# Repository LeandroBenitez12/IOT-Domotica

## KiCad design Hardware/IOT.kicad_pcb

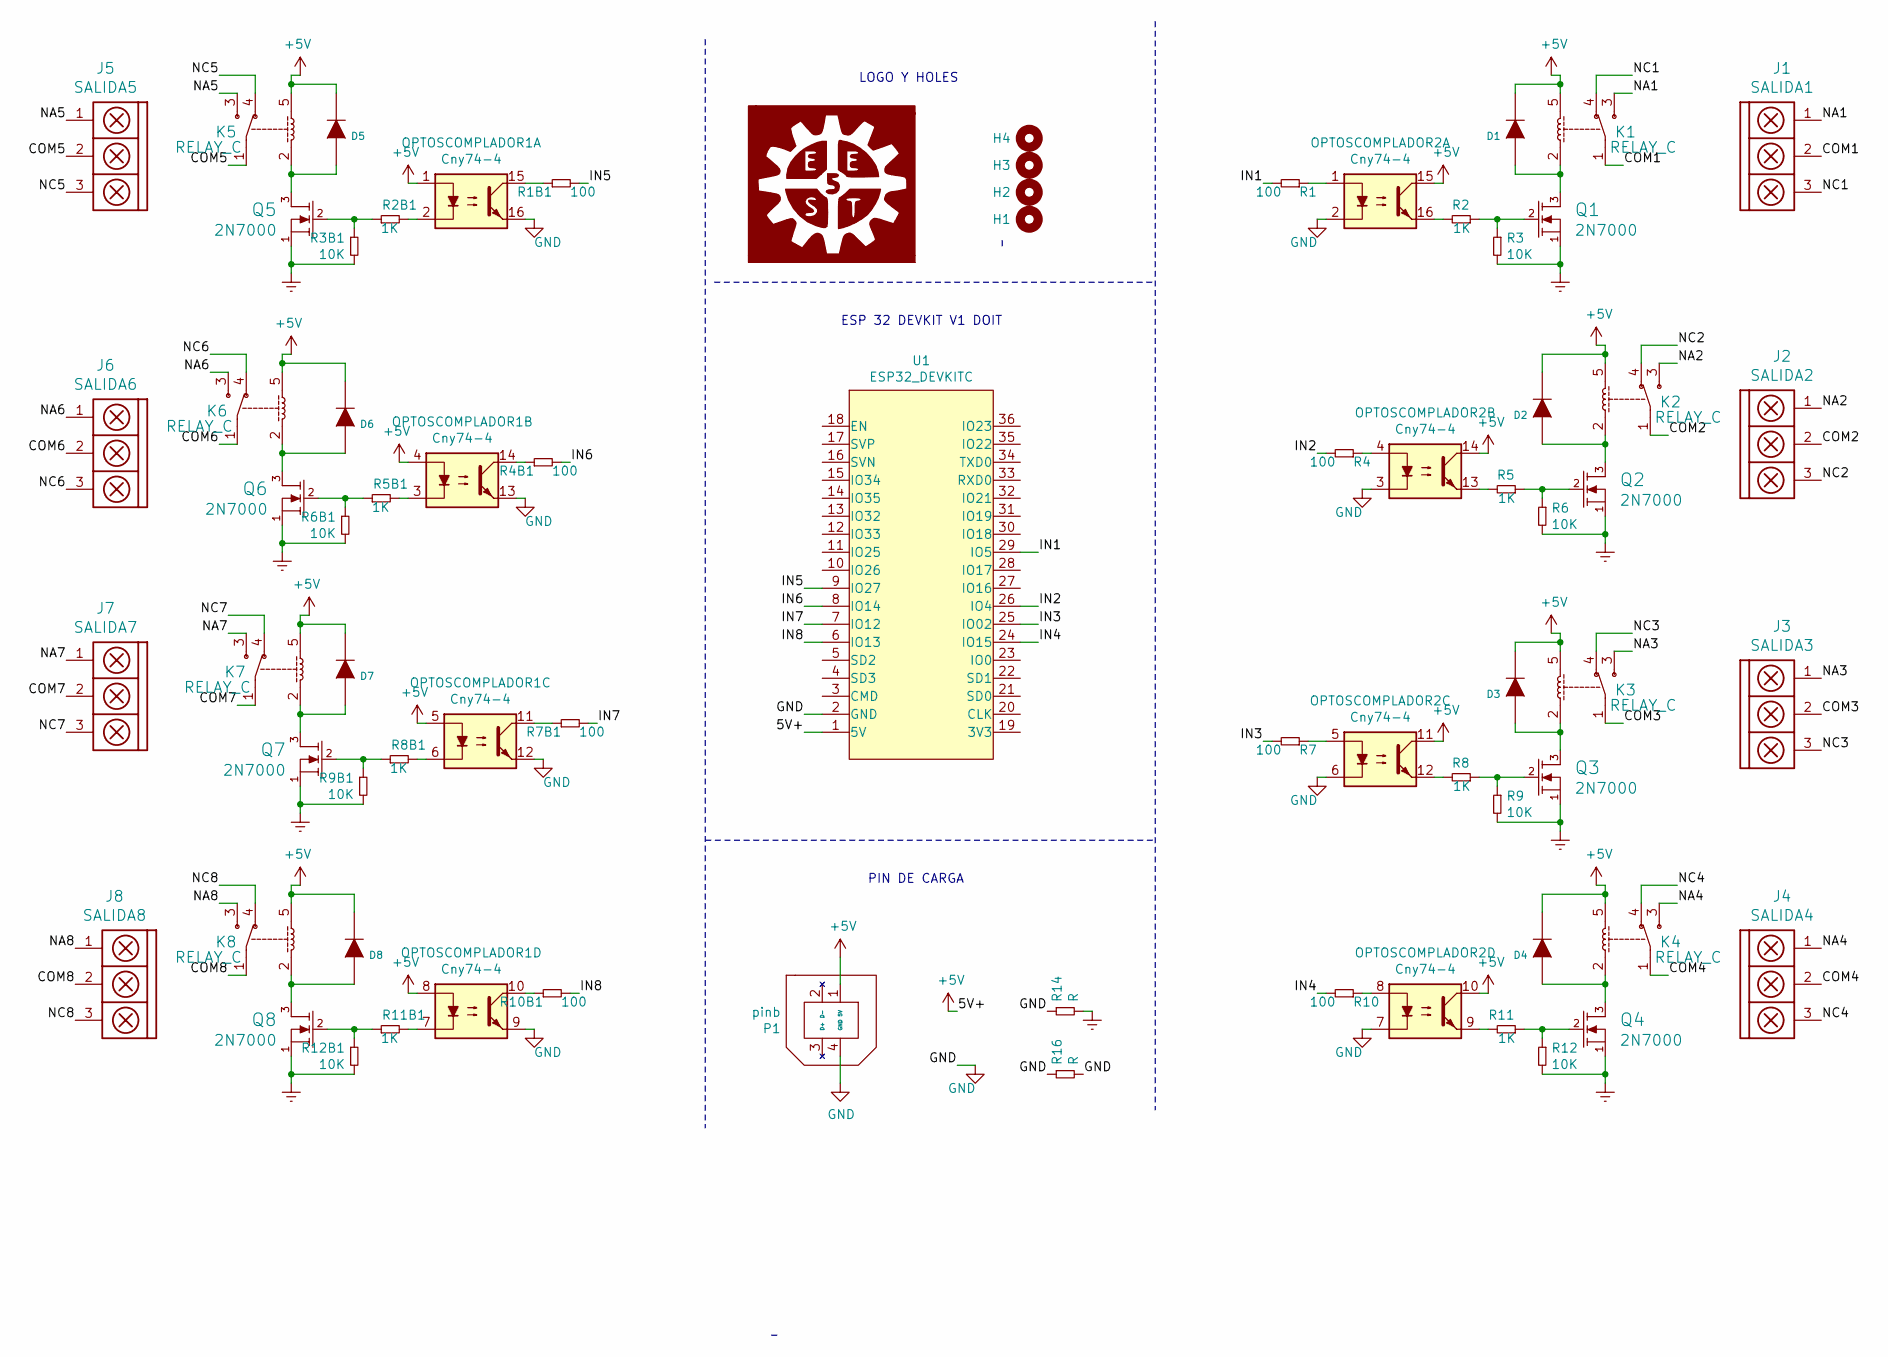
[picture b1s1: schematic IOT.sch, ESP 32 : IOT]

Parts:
D1, D2, D3, D4, D5, D6, D7, D8: DIODE; DO-41
G1: Logo_EESTN5; LOGO_EESTN5
H1, H2, H3, H4: Mounting_Hole; hole_2mm
J1: SALIDA1; BORNERA3_AZUL
J2: SALIDA2; BORNERA3_AZUL
J3: SALIDA3; BORNERA3_AZUL
J4: SALIDA4; BORNERA3_AZUL
J5: SALIDA5; BORNERA3_AZUL
J6: SALIDA6; BORNERA3_AZUL
J7: SALIDA7; BORNERA3_AZUL
J8: SALIDA8; BORNERA3_AZUL
K1, K2, K3, K4, K5, K6, K7, K8: RELAY_C; Relay_C
OPTOSCOMPLADOR1, OPTOSCOMPLADOR2: Cny74-4; DIP_16-300
P1: pinb; USB_B
Q1, Q2, Q3, Q4, Q5, Q6, Q7, Q8: 2N7000; to92
R1, R1B1, R4, R4B1, R7, R7B1, R10, R10B1: 100; RES0.3
R2, R2B1, R5, R5B1, R8, R8B1, R11, R11B1: 1K; RES0.3
R3, R3B1, R6, R6B1, R9, R9B1, R12, R12B1: 10K; RES0.3
R14, R16: R; RES0.3
U1: ESP32_DEVKITC; ESP32_DEVKITC1

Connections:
+5V: D1.2 (K), D2.2 (K), D3.2 (K), D4.2 (K), D5.2 (K), D6.2 (K), D7.2 (K), D8.2 (K), K1.5, K2.5, K3.5, K4.5, K5.5, K6.5, K7.5, K8.5, OPTOSCOMPLADOR1.1, OPTOSCOMPLADOR1.4, OPTOSCOMPLADOR1.5, OPTOSCOMPLADOR1.8, OPTOSCOMPLADOR2.10, OPTOSCOMPLADOR2.11, OPTOSCOMPLADOR2.14, OPTOSCOMPLADOR2.15, P1.1 (5V), U1.1 (5V)
/COM1: J1.2, K1.1
/COM2: J2.2, K2.1
/COM3: J3.2, K3.1
/COM4: J4.2, K4.1
/COM5: J5.2, K5.1
/COM6: J6.2, K6.1
/COM7: J7.2, K7.1
/COM8: J8.2, K8.1
/IN1: R1.2, U1.29 (IO5)
/IN2: R4.2, U1.26 (IO4)
/IN3: R7.2, U1.25 (IO02)
/IN4: R10.2, U1.24 (IO15)
/IN5: R1B1.2, U1.9 (IO27)
/IN6: R4B1.2, U1.8 (IO14)
/IN7: R7B1.2, U1.7 (IO12)
/IN8: R10B1.2, U1.6 (IO13)
/NA1: J1.1, K1.3
/NA2: J2.1, K2.3
/NA3: J3.1, K3.3
/NA4: J4.1, K4.3
/NA5: J5.1, K5.3
/NA6: J6.1, K6.3
/NA7: J7.1, K7.3
/NA8: J8.1, K8.3
/NC1: J1.3, K1.4
/NC2: J2.3, K2.4
/NC3: J3.3, K3.4
/NC4: J4.3, K4.4
/NC5: J5.3, K5.4
/NC6: J6.3, K6.4
/NC7: J7.3, K7.4
/NC8: J8.3, K8.4
GND: OPTOSCOMPLADOR1.9, OPTOSCOMPLADOR1.12, OPTOSCOMPLADOR1.13, OPTOSCOMPLADOR1.16, OPTOSCOMPLADOR2.2, OPTOSCOMPLADOR2.3, OPTOSCOMPLADOR2.6, OPTOSCOMPLADOR2.7, P1.4 (GND), R14.1, R16.1, R16.2, U1.2 (GND)
unnamed: D1.1 (A), K1.2, Q1.3 (D)
unnamed: D2.1 (A), K2.2, Q2.3 (D)
unnamed: D3.1 (A), K3.2, Q3.3 (D)
unnamed: D4.1 (A), K4.2, Q4.3 (D)
unnamed: D5.1 (A), K5.2, Q5.3 (D)
unnamed: D6.1 (A), K6.2, Q6.3 (D)
unnamed: D7.1 (A), K7.2, Q7.3 (D)
unnamed: D8.1 (A), K8.2, Q8.3 (D)
unnamed: OPTOSCOMPLADOR1.2, R2B1.2
unnamed: OPTOSCOMPLADOR1.3, R5B1.2
unnamed: OPTOSCOMPLADOR1.6, R8B1.2
unnamed: OPTOSCOMPLADOR1.7, R11B1.2
unnamed: OPTOSCOMPLADOR1.10, R10B1.1
unnamed: OPTOSCOMPLADOR1.11, R7B1.1
unnamed: OPTOSCOMPLADOR1.14, R4B1.1
unnamed: OPTOSCOMPLADOR1.15, R1B1.1
unnamed: OPTOSCOMPLADOR2.1, R1.1
unnamed: OPTOSCOMPLADOR2.4, R4.1
unnamed: OPTOSCOMPLADOR2.5, R7.1
unnamed: OPTOSCOMPLADOR2.8, R10.1
unnamed: OPTOSCOMPLADOR2.9, R11.2
unnamed: OPTOSCOMPLADOR2.12, R8.2
unnamed: OPTOSCOMPLADOR2.13, R5.2
unnamed: OPTOSCOMPLADOR2.16, R2.2
unnamed: Q1.2 (G), R2.1, R3.1
unnamed: Q2.2 (G), R5.1, R6.1
unnamed: Q3.2 (G), R8.1, R9.1
unnamed: Q4.2 (G), R11.1, R12.1
unnamed: Q5.2 (G), R2B1.1, R3B1.1
unnamed: Q6.2 (G), R5B1.1, R6B1.1
unnamed: Q7.2 (G), R8B1.1, R9B1.1
unnamed: Q8.2 (G), R11B1.1, R12B1.1

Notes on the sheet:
ESP 32 DEVKIT V1 DOIT
LOGO Y HOLES
PIN DE CARGA

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
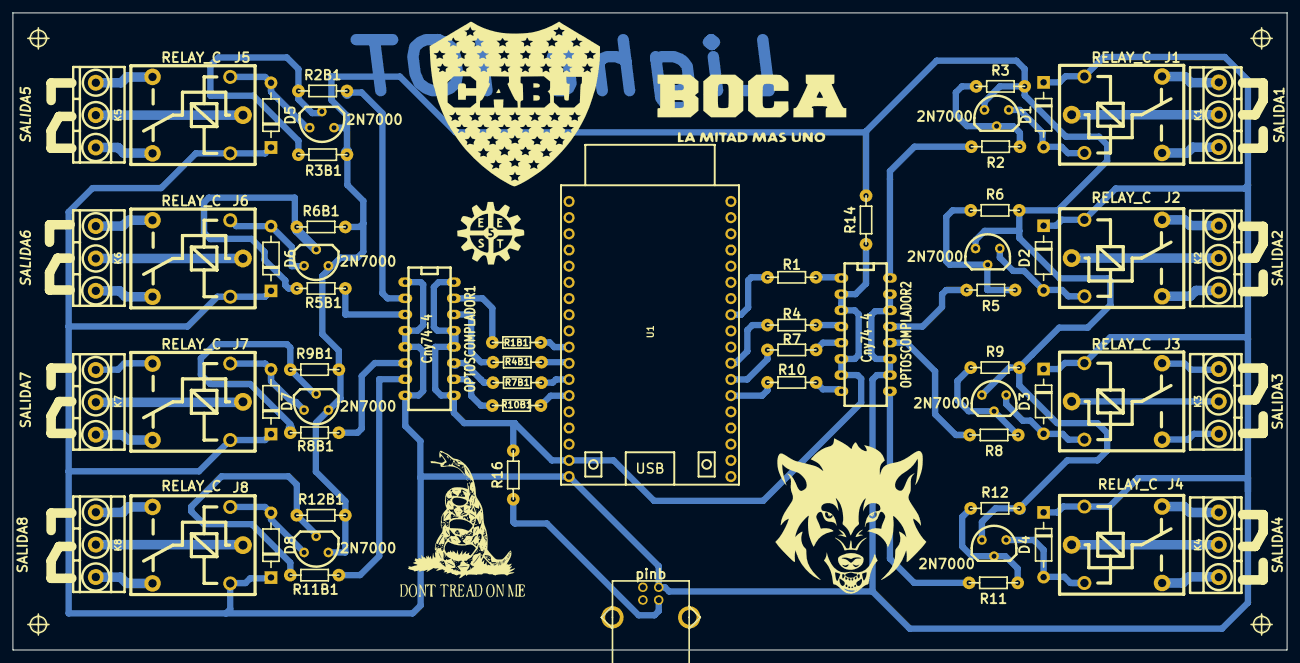
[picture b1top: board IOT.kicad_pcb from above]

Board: 2 copper layers, 200.0 x 100.0 mm, 67 parts (0 on the bottom side), 67 nets.

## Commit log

2022-08-19 Subiendo los archivos
